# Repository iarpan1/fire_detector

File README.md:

# 🚨 ESP32-Based Fire & Gas Monitoring System — RTOS-Driven Embedded Design 🚨

A standalone embedded fire and gas monitoring system emphasizing **power integrity**, **RF-aware PCB layout**, and **deterministic real-time behavior** using **FreeRTOS**.  

The system integrates **sensing, processing, and cellular communication** on a single expansion PCB, enabling reliable operation **without external network dependency**.  

---

## ⚡ MCU & RTOS
- **ESP32 dual-core** running FreeRTOS  
- Tasks separated for **deterministic response** and **fault isolation**:  
  - Sensor acquisition  
  - Event evaluation / threshold logic  
  - GSM communication (AT command handling)  
  - Alert & retry management  
- **RTOS queues and semaphores** synchronize sensor events and communication states  
- **Watchdog supervision** ensures task-level fault recovery  

---

## 📡 Cellular Communication
- **GSM800L quad-band module (2G)**  
- UART interface controlled via RTOS task  
- Power design accommodates **~2A peak TX current** during GSM bursts  
- Local **bulk and low-ESR decoupling** reduces voltage sag  
- Enables **SMS-based alerting independent of Wi-Fi or cloud services**  

---

## 🔥 Sensor Subsystem
- Flame sensor for **fast IR fire detection**  
- MQ-2 gas/smoke sensor for **combustible gas detection**  
- DHT11 for **temperature & humidity context**, helping reduce false alarms  

---

## 🔋 Power & Reliability
- On-board **18650 Li-ion battery** for autonomous operation  
- Power domains partitioned between:  
  - RF load (GSM)  
  - Digital logic (ESP32)  
  - Analog sensing  
- Ensures **MCU stability during RF current spikes**  
- System remains operational during mains power failure  

---

## 🛠 PCB & Integration
- Modular expansion-board layout  
- **Wide, low-impedance power traces** for RF paths  
- Continuous ground reference for **noise control**  
- Reduced wiring and connector failure points  

---

## 🎯 Engineering Objective
Deliver a **deployable, real-world embedded safety system** with:  
- RTOS-based **task determinism**  
- Reliable **alert delivery**  
- **Power-aware hardware design**  
- Clean **firmware–hardware co-design**  

---

## 📂 Repository Contents
- `hardware/` — PCB schematics, Gerber files, and BOM  
- `firmware/` — FreeRTOS-based ESP32 firmware  
- `docs/` — RTOS task diagrams, scheduler priorities, and system design notes  
- `README.md` — Project overview and documentation  

---

## 🔗 Resources
- Open-source schematics, PCB, and RTOS firmware: [GitHub Repository](https://github.com/iarpan1/fire_detector)  

---

## 🏷 Tags
`EmbeddedSystems` `RTOS` `FreeRTOS` `ESP32` `HardwareDesign` `GSM` `PCBDesign` `PowerIntegrity` `FireSafety` `ElectronicsEngineering` `OpenSource`

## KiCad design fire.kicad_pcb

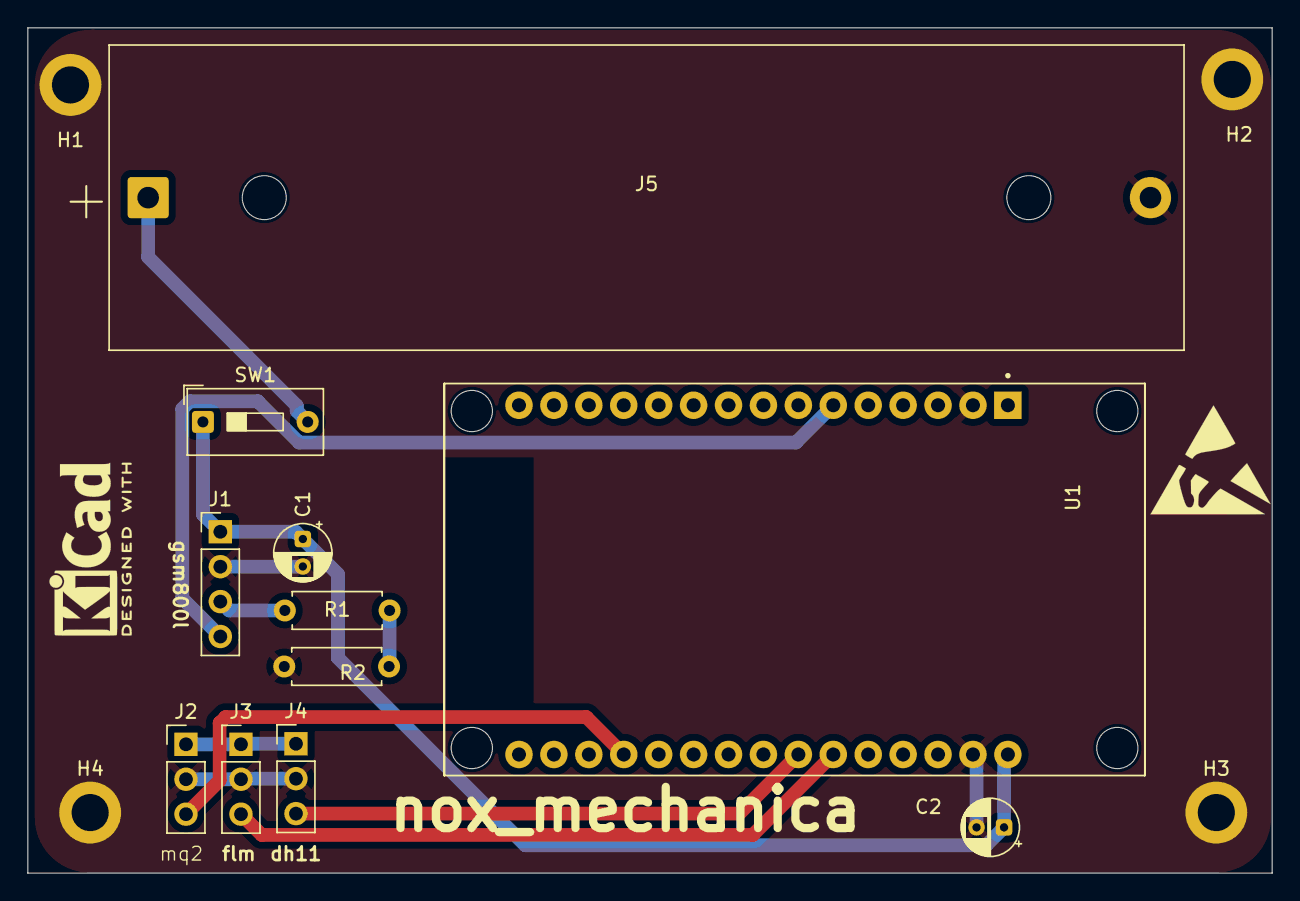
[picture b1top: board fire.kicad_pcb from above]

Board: 2 copper layers, 90.5 x 61.5 mm, 15 parts (0 on the bottom side), 10 nets.

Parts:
C1: 1000uF; CP_Radial_D4.0mm_P2.00mm
C2: 100uF; CP_Radial_D4.0mm_P2.00mm
H1, H2, H3, H4: MountingHole_Pad; MountingHole_2.7mm_M2.5_ISO7380_Pad
J1: gsm800l; PinHeader_1x04_P2.54mm_Vertical
J2: mq2; PinHeader_1x03_P2.54mm_Vertical
J3: flame sensor; PinHeader_1x03_P2.54mm_Vertical
J4: dh11; PinHeader_1x03_P2.54mm_Vertical
J5: Conn_01x02_Socket; BatteryHolder_MPD_BK-18650-PC2
R1: 10k; R_Axial_DIN0207_L6.3mm_D2.5mm_P7.62mm_Horizontal
R2: 20k; R_Axial_DIN0207_L6.3mm_D2.5mm_P7.62mm_Horizontal
SW1: SW_DPST_x2; SW_DIP_SPSTx01_Slide_9.78x4.72mm_W7.62mm_P2.54mm
U1: ESP32-DEVKIT-V1; MODULE_ESP32_DEVKIT_V1

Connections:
26: J4.3, U1.24 (D26)
27: J3.3, U1.25 (D27)
34: J2.3, U1.19 (D34)
+3.3V: J2.1, J3.1, J4.1, U1.1 (3V3)
+BATT: J5.1, SW1.2 (B)
GND: C1.2, C2.2, H1.1, H2.1, H3.1, H4.1, J1.2, J2.2, J3.2, J4.2, J5.2, R2.2, U1.2 (GND), U1.29 (GND)
unnamed: J1.3, R1.1
VCC: C1.1, C2.1, J1.1, SW1.1 (A), U1.30 (VIN)
rx: R1.2, R2.1, U1.7 (TX2)
tx: J1.4, U1.6 (RX2)

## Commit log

2026-01-03 Add README for ESP32 Fire & Gas Monitoring System
    Added comprehensive documentation for the ESP32-based fire and gas monitoring system, detailing its architecture, components, and operational objectives.
